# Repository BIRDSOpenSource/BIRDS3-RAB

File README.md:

<div align="center">
  
</div>

# BIRDS3-RAB
 Documentation for the Rear Access Board used in the BIRDS3 Satellite

## About the BIRDS3 Program:

The project was led by Kyushu Institute of Technology in Japan and involves students from Sri Lanka, Bhutan, Nepal and Japan.
Satellite Names: NepaliSat-1 (Nepal), Raavana-1 (Sri Lanka) and Ugiusu (Japan)

Stakeholders: Nepal Academy of Science and Technology (NAST) for Nepal, Arthur C Clarke Institute for Modern Technologies (ACCIMT) for Sri Lanka, and Kyushu Institute of Technology (Kyutech) for Japan.

Project duration: 2018-2020

CubeSat: 1U (10x10x10) cm3

Weight: 1.13kg

Launch Date: 17th April 2019

BIRDS-3 has 4 main missions in total; LoRa Demonstration Mission (LDM), Imaging Mission (CAM), Attitude Determination and Control Mission (ADCS) and Software Configurable Backplane Mission (BPB) 

## Organisation structure

## Features

## I like this project, can I help you?
You are welcome 🙂

* Give us a star ⭐
* Watch repository to be notified about updates 👀
* If you will find some errors, report them in Issues 🐞
* Try Birds designs on some real computer and let us know how it worked in Discussions. 💬
* We would greatly appreciate if you would also tell others about this ecosystem, it helps us to improve BIRDS Open Source. Thank you!

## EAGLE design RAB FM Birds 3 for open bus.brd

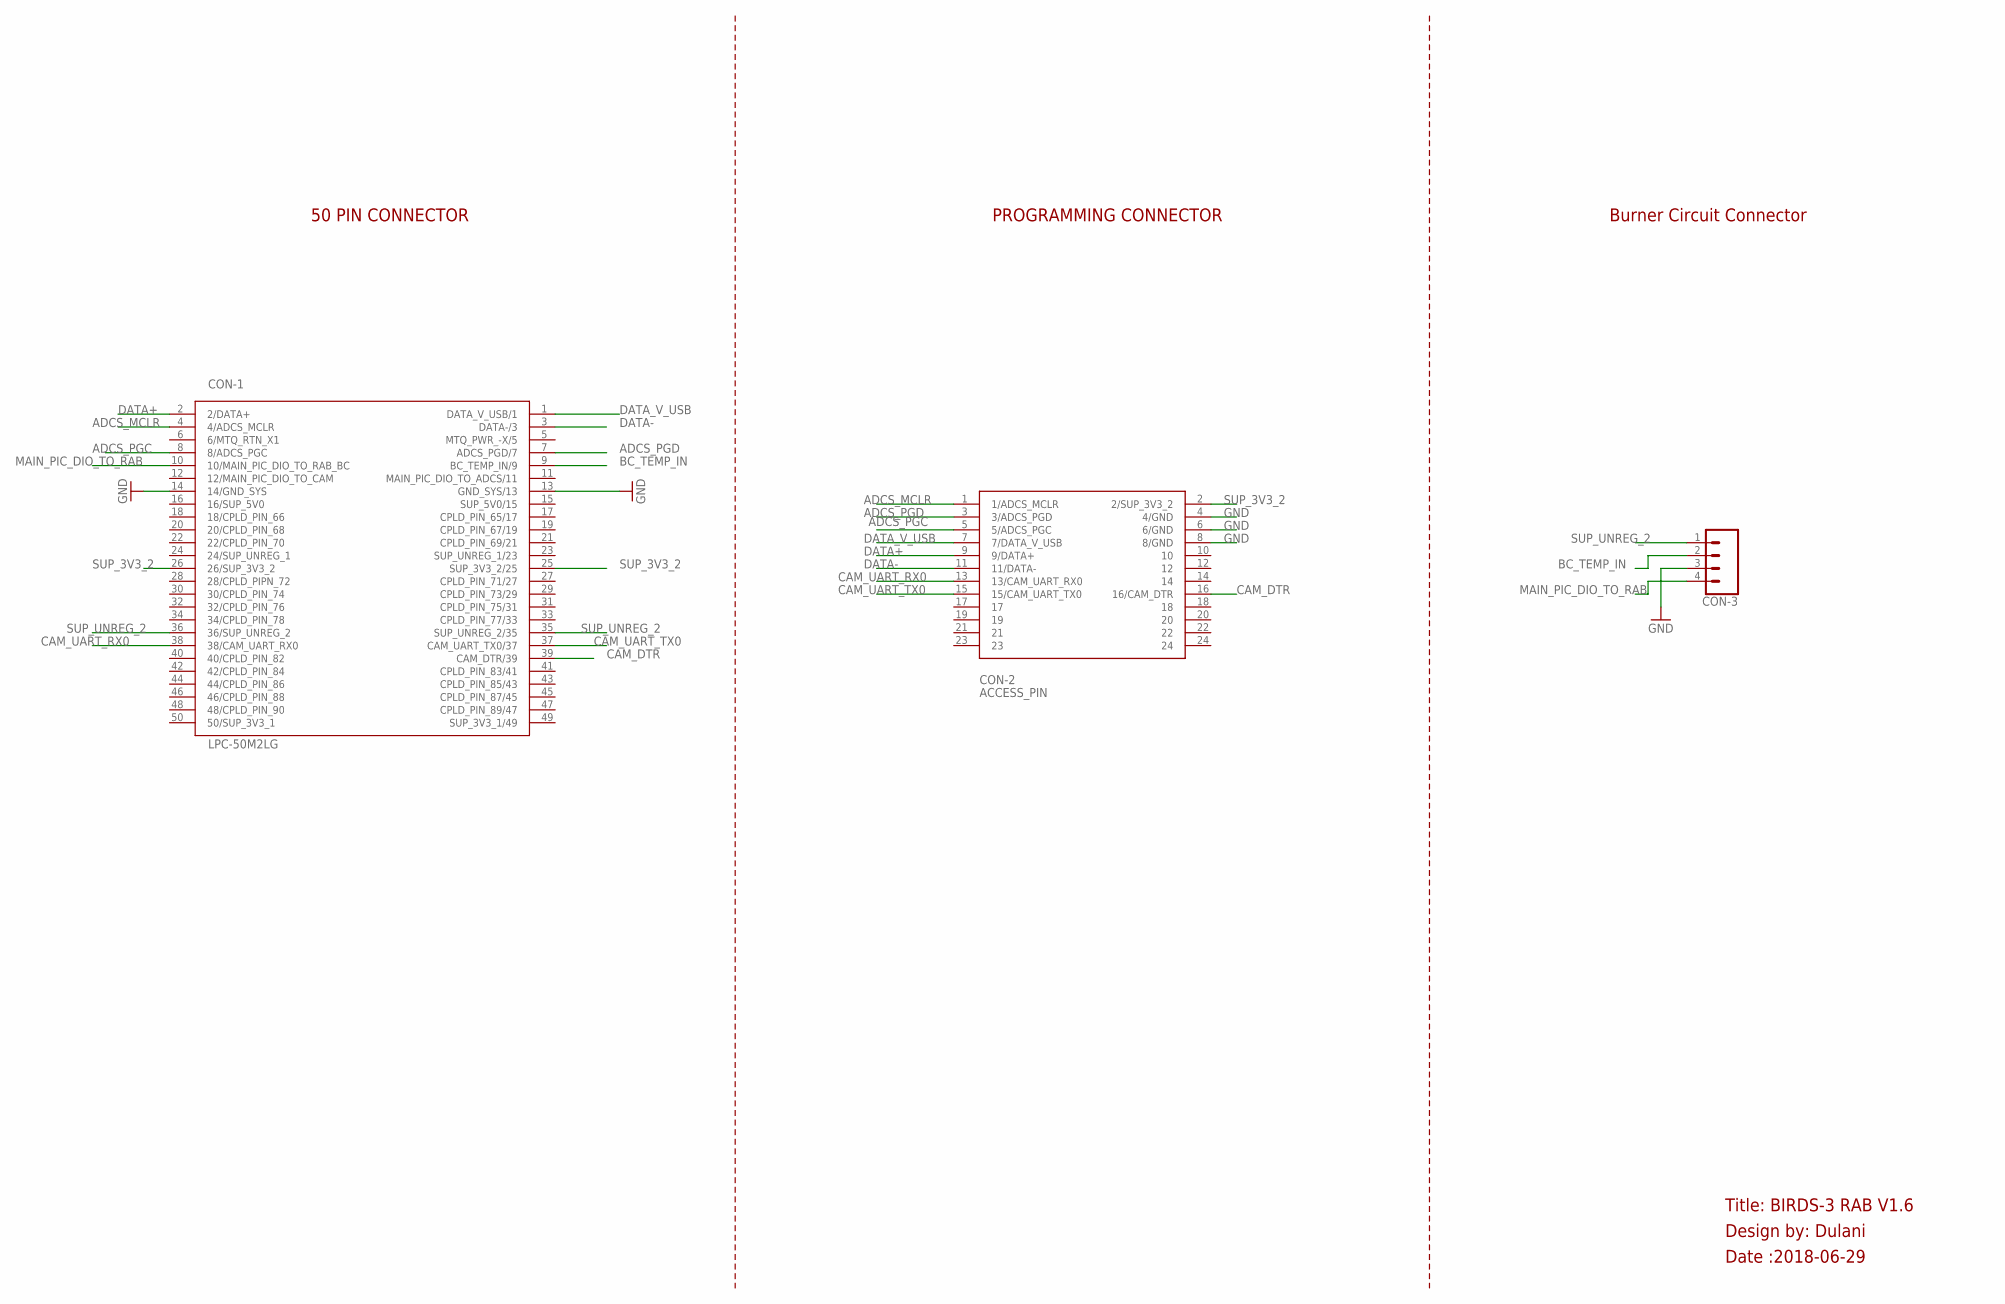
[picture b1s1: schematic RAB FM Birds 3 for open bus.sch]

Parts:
CON-1: LPC-50M2LG
CON-2: ACCESS_PIN; SMD24
CON-3: CONN_04JST-PTH; JST-4-PTH

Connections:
ADCS_MCLR: CON-1.4 (4/ADCS_MCLR), CON-2.1 (1/ADCS_MCLR)
ADCS_PGC: CON-1.8 (8/ADCS_PGC), CON-2.5 (5/ADCS_PGC)
ADCS_PGD: CON-1.7 (ADCS_PGD/7), CON-2.3 (3/ADCS_PGD)
BC_TEMP_IN: CON-1.9 (BC_TEMP_IN/9), CON-3.2
CAM_DTR: CON-1.39 (CAM_DTR/39), CON-2.16 (16/CAM_DTR)
CAM_UART_RX0: CON-1.38 (38/CAM_UART_RX0), CON-2.13 (13/CAM_UART_RX0)
CAM_UART_TX0: CON-1.37 (CAM_UART_TX0/37), CON-2.15 (15/CAM_UART_TX0)
DATA+: CON-1.2 (2/DATA+), CON-2.9 (9/DATA+)
DATA-: CON-1.3 (DATA-/3), CON-2.11 (11/DATA-)
DATA_V_USB: CON-1.1 (DATA_V_USB/1), CON-2.7 (7/DATA_V_USB)
GND: CON-1.13 (GND_SYS/13), CON-1.14 (14/GND_SYS), CON-2.4 (4/GND), CON-2.6 (6/GND), CON-2.8 (8/GND), CON-3.3
MAIN_PIC_DIO_TO_RAB: CON-1.10 (10/MAIN_PIC_DIO_TO_RAB_BC), CON-3.4
SUP_3V3_2: CON-1.25 (SUP_3V3_2/25), CON-1.26 (26/SUP_3V3_2), CON-2.2 (2/SUP_3V3_2)
SUP_UNREG_2: CON-1.35 (SUP_UNREG_2/35), CON-1.36 (36/SUP_UNREG_2), CON-3.1

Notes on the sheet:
Title: BIRDS-3 RAB V1.6
Design by: Dulani
Date :2018-06-29
50 PIN CONNECTOR
Burner Circuit Connector
PROGRAMMING CONNECTOR

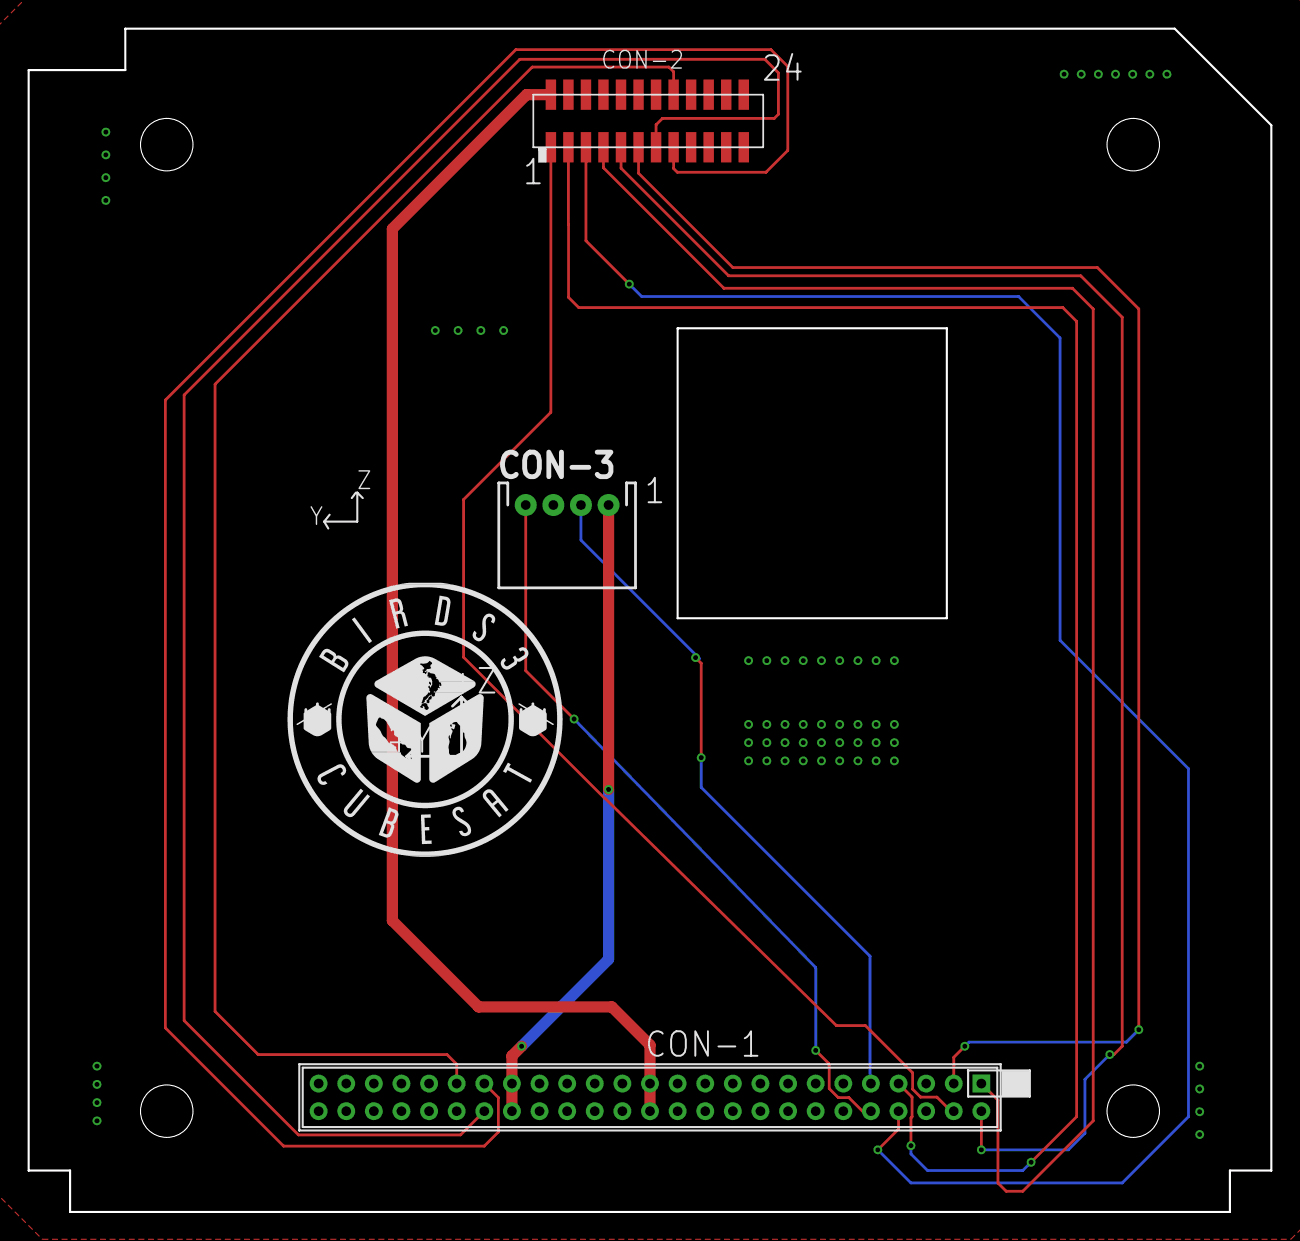
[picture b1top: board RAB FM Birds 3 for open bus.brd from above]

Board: 4 copper layers, 90.0 x 85.7 mm, 3 parts (1 on the bottom side), 14 nets.

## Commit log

2021-10-20 Update LICENSE

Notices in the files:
parts and their libraries:
SparkFun-Connectors: Licensing: Creative Commons ShareAlike 4.0 International - https://creativecommons.org/licenses/by-sa/4.0
